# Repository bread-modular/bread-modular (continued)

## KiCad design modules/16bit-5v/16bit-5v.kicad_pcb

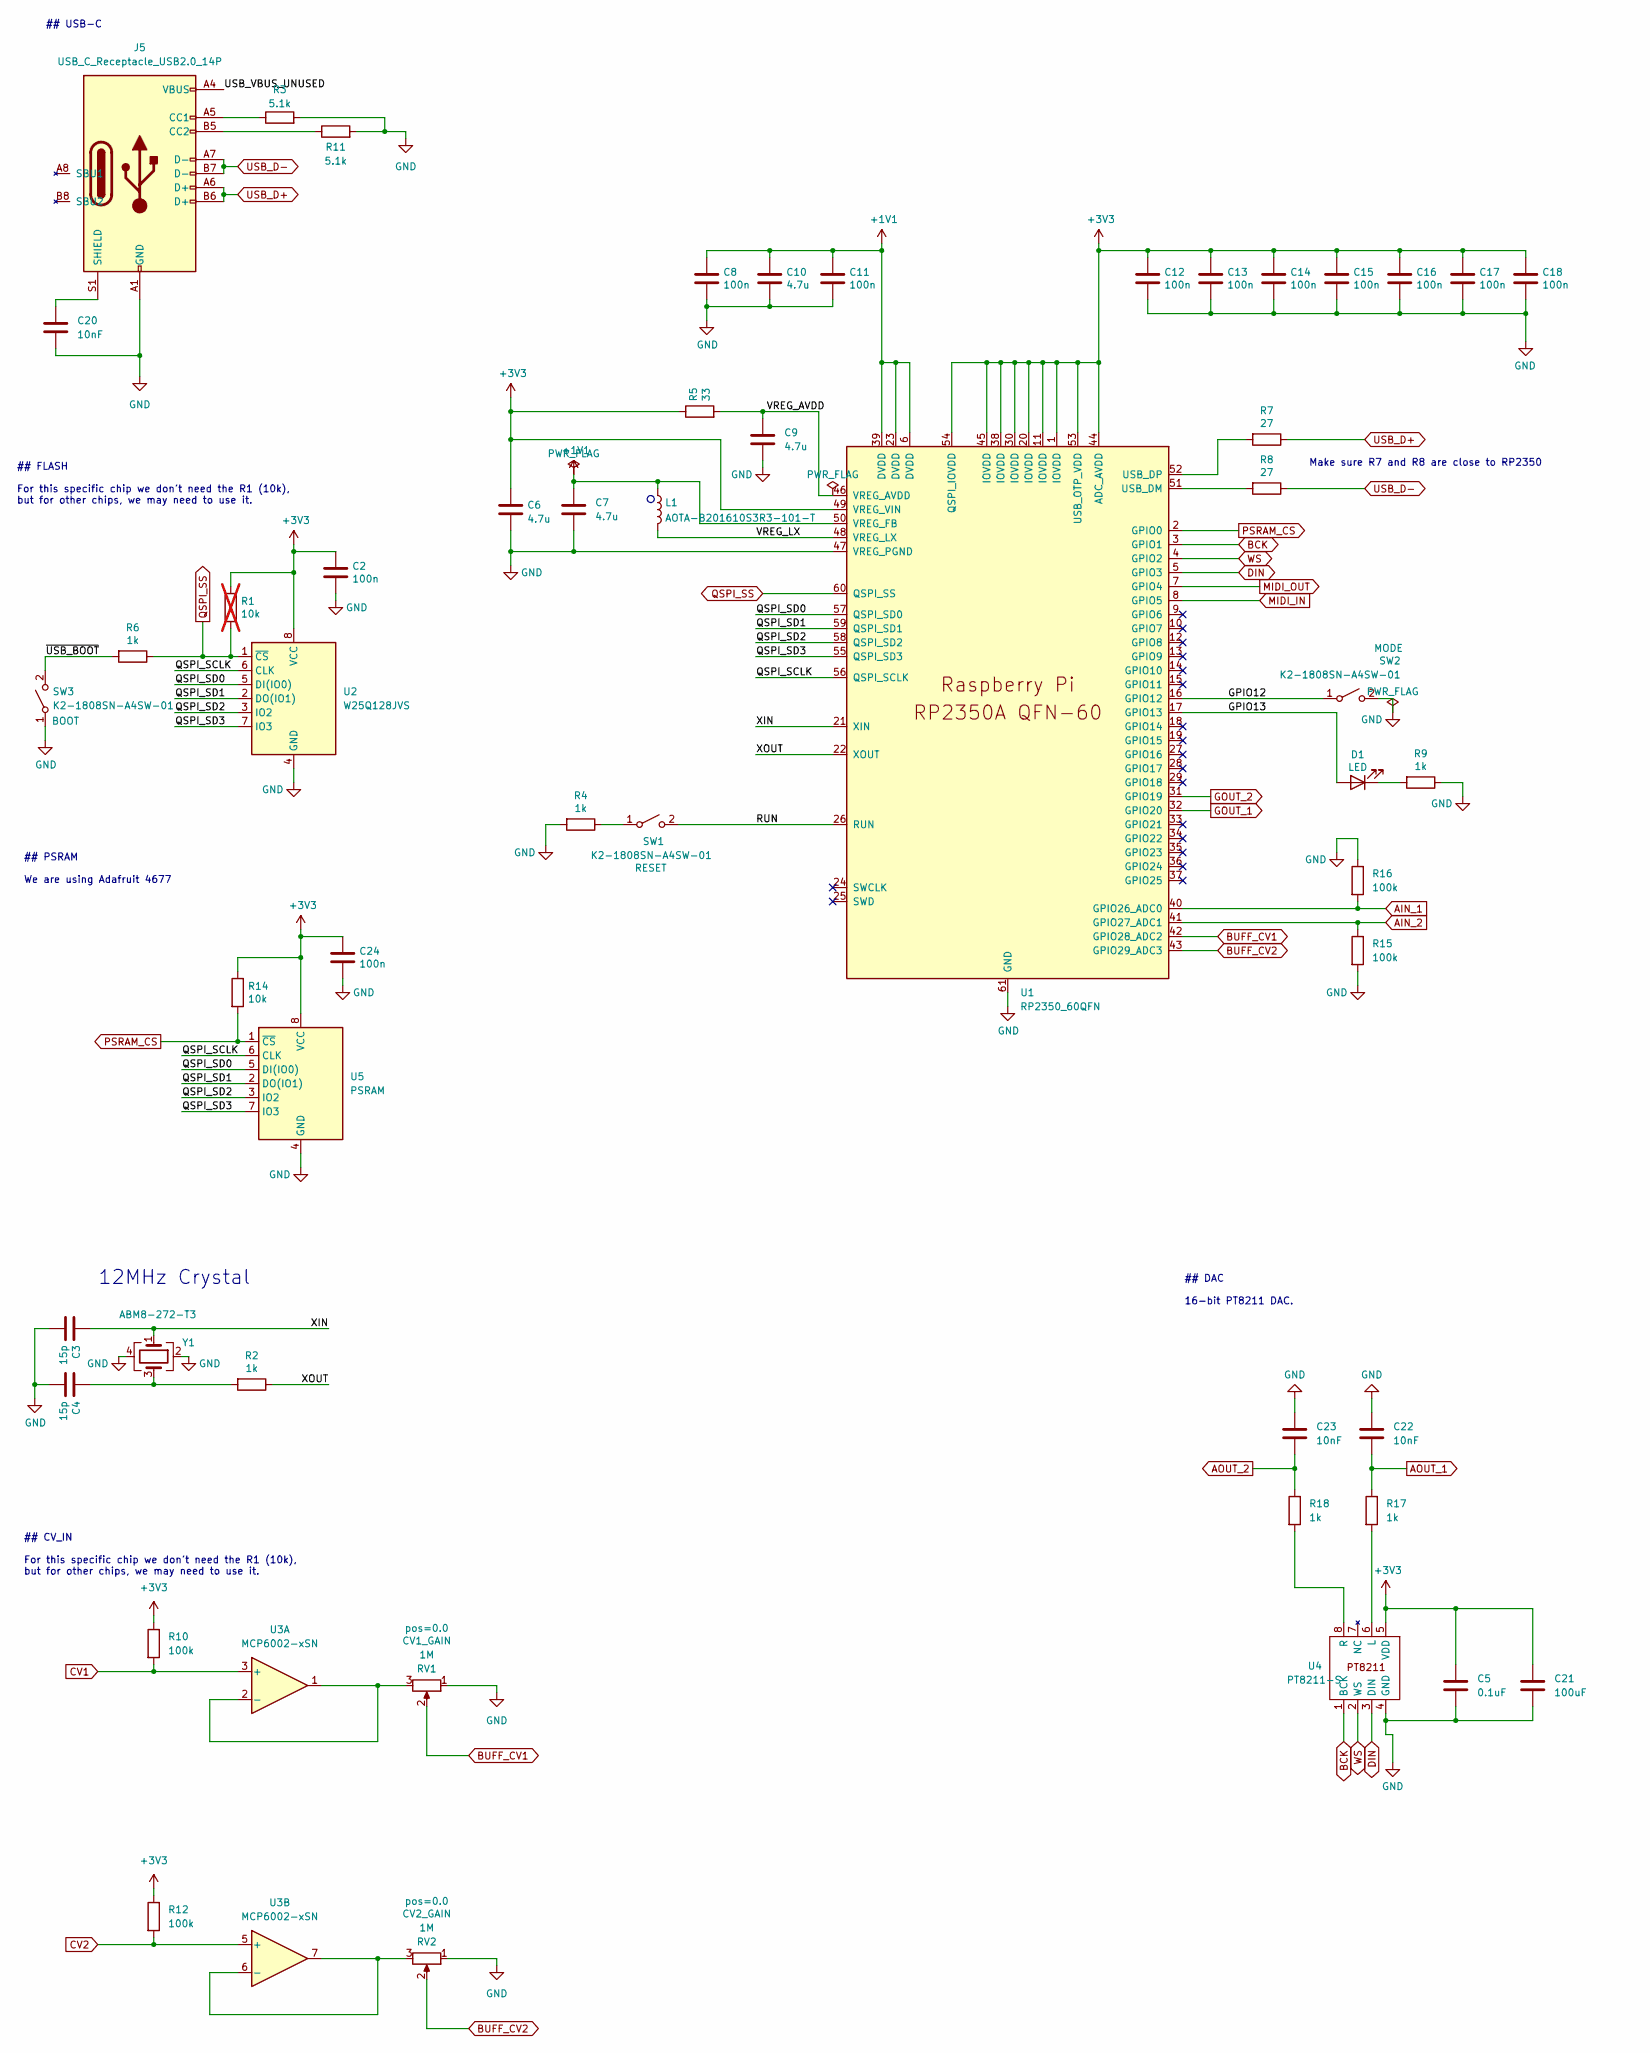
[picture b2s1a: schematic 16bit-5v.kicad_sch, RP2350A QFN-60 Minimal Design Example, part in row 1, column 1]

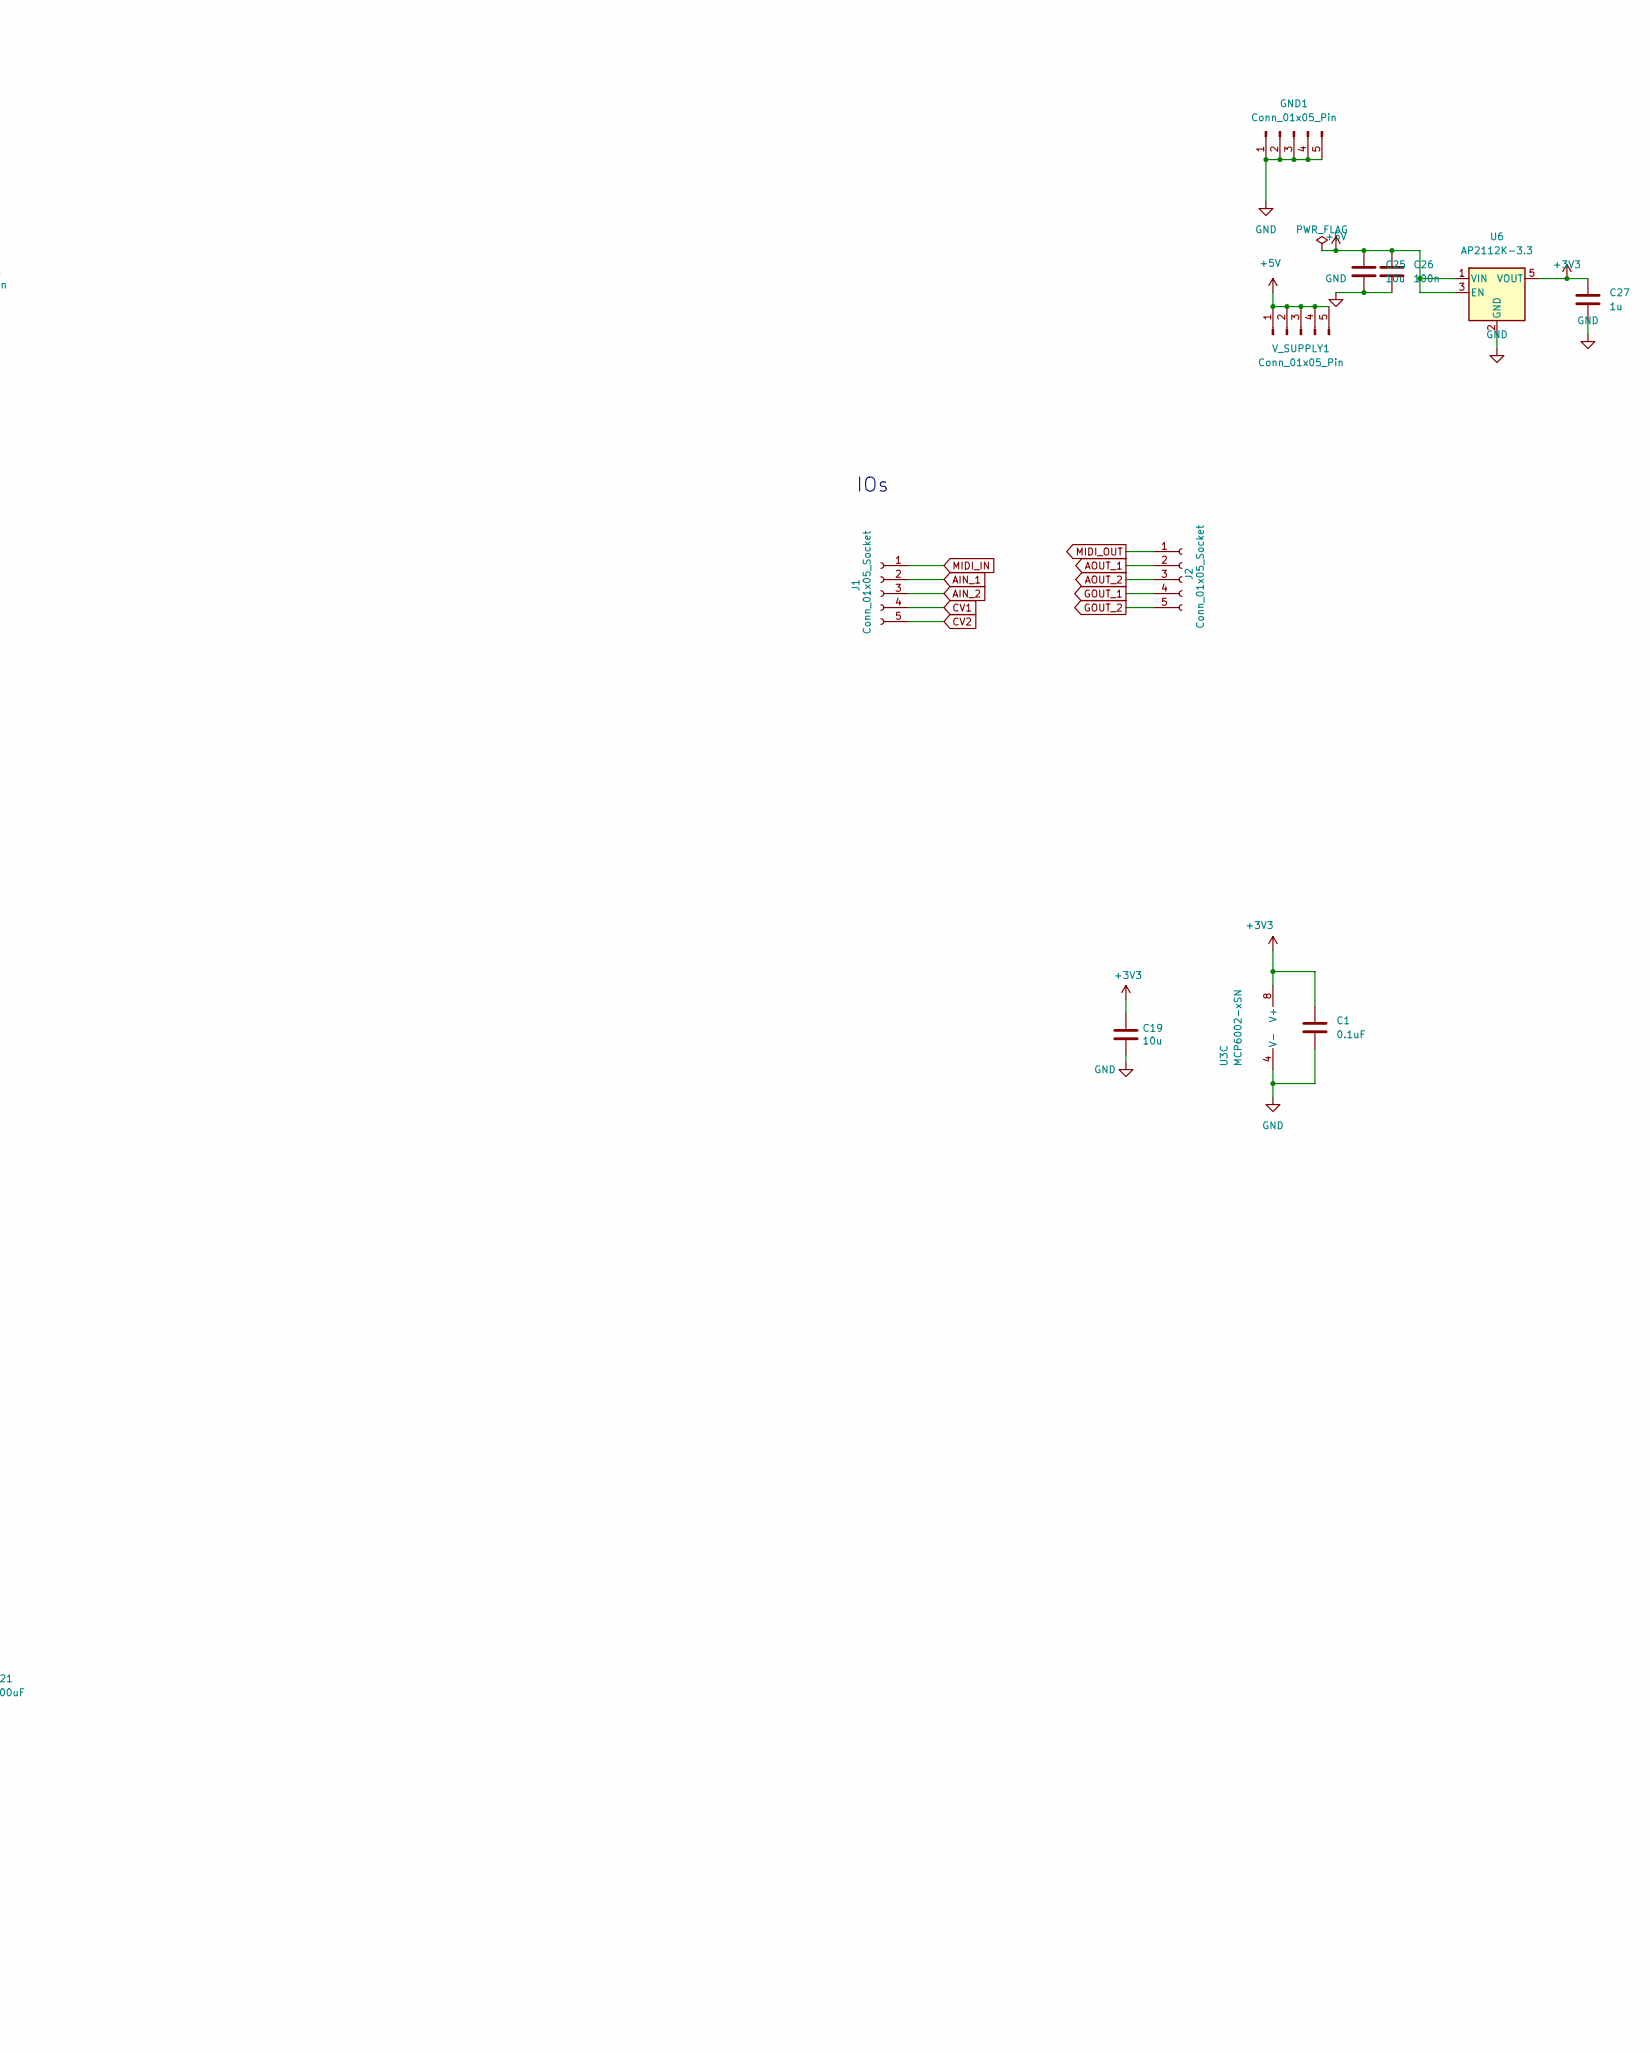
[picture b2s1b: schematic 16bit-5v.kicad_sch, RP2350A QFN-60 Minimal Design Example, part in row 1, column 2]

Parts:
C1, C5: 0.1uF; C_0402_1005Metric; Voltage Rating 16 V; Tolerance ±10%; MPN CL05B104KO5NNNC; LCSC C1525
C2, C8, C11, C12, C13, C14, C15, C16, C17, C18, C24, C26: 100n; C_0402_1005Metric; Voltage Rating 16 V; Tolerance ±10%; MPN CL05B104KO5NNNC; LCSC C1525
C3, C4: 15p; C_0402_1005Metric; Voltage Rating 50 V; Tolerance ±5%; MPN 0402CG150J500NT; LCSC C1548
C6, C7: 4.7u; C_0402_1005Metric_small_pads; Voltage Rating 10 V; Tolerance ±20%; MPN CL05A475MP5NRNC; LCSC C23733
C9, C10: 4.7u; C_0402_1005Metric; Voltage Rating 10 V; Tolerance ±20%; MPN CL05A475MP5NRNC; LCSC C23733
C19, C25: 10u; C_0805_2012Metric; Voltage Rating 25 V; Tolerance ±10%; MPN CL21A106KAYNNNE; LCSC C15850
C20: 10nF; C_0805_2012Metric; Voltage Rating 50 V; Tolerance ±10%; MPN CL21B103KBANNNC; LCSC C1710
C21: 100uF; C_1206_3216Metric; Voltage Rating 6.3 V; Tolerance ±20%; MPN CL31A107MQHNNNE; LCSC C15008
C22, C23: 10nF; C_0402_1005Metric; Voltage Rating 50 V; Tolerance ±10%; MPN CL05B103KB5NNNC; LCSC C15195
C27: 1u; C_0805_2012Metric; Voltage Rating 50 V; Tolerance ±10%; MPN CL21B105KBFNNNE; LCSC C28323
D1: LED; LED_0603_1608Metric
GND1: Conn_01x05_Pin; PinHeader_1x05_P2.54mm_Vertical
J1, J2: Conn_01x05_Socket; PinSocket_1x05_P2.54mm_Vertical
J5: USB_C_Receptacle_USB2.0_14P; HRO-TYPE-C-31-M-12; MPN TYPE-C-31-M-12; JLCPCB Position Offset X 0
L1: AOTA-B201610S3R3-101-T; L_pol_2016; MPN AOTA-B201610S3R3-101-T; LCSC C42411119
R1: 10k; R_0402_1005Metric; not fitted
R2, R4, R6, R9, R17, R18: 1k; R_0402_1005Metric; Voltage Rating 50 V; Tolerance ±1%; MPN 0402WGF1001TCE; LCSC C11702
R3, R11: 5.1k; R_0603_1608Metric; Voltage Rating 75 V; Tolerance ±1%; MPN 0603WAF5101T5E; LCSC C23186
R5: 33; R_0402_1005Metric; Voltage Rating 50 V; Tolerance ±1%; MPN 0402WGF330JTCE; LCSC C25105
R7, R8: 27; R_0402_1005Metric
R10, R12, R15, R16: 100k; R_0402_1005Metric; Voltage Rating 50 V; Tolerance ±1%; MPN 0402WGF1003TCE; LCSC C25741
R14: 10k; R_0402_1005Metric; Voltage Rating 50 V; Tolerance ±1%; MPN 0402WGF1002TCE; LCSC C25744
RV1, RV2: 1M; Potentiometer_RV09
SW1, SW2, SW3: K2-1808SN-A4SW-01; MPN K2-1808SN-A4SW-01; LCSC C92589
U1: RP2350_60QFN; RP2350-QFN-60-1EP_7x7_P0.4mm_EP3.4x3.4mm_ThermalVias; MPN RP2350A; LCSC C42411118
U2: W25Q128JVS; SOIC-8_5.23x5.23mm_P1.27mm; MPN W25Q128JVSIQ; LCSC C97521
U3: MCP6002-xSN; SOIC-8_3.9x4.9mm_P1.27mm; MPN MCP6002-I/SN; LCSC C116706
U4: PT8211-S; SOIC-8_3.9x4.9mm_P1.27mm; MPN PT8211-S; LCSC C92004
U5: PSRAM; SOIC-8 Generic
U6: AP2112K-3.3; SOT-23-5; MPN AP2112K-3.3TRG1; LCSC C51118
V_SUPPLY1: Conn_01x05_Pin; PinHeader_1x05_P2.54mm_Vertical
Y1: ABM8-272-T3; Crystal_SMD_3225-4Pin_3.2x2.5mm; MPN ABM8-272-T3; LCSC C20625731

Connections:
+1V1: C7.1, C8.1, C10.1, C11.1, L1.1, U1.6 (DVDD), U1.23 (DVDD), U1.39 (DVDD), U1.50 (VREG_FB)
+3V3: C1.1, C2.1, C5.1, C6.1, C12.1, C13.1, C14.1, C15.1, C16.1, C17.1, C18.1, C19.1, C21.1, C24.1, C27.1, R1.1, R5.1, R10.1, R12.1, R14.1, U1.1 (IOVDD), U1.11 (IOVDD), U1.20 (IOVDD), U1.30 (IOVDD), U1.38 (IOVDD), U1.44 (ADC_AVDD), U1.45 (IOVDD), U1.49 (VREG_VIN), U1.53 (USB_OTP_VDD), U1.54 (QSPI_IOVDD), U2.8 (VCC), U3.8 (V+), U4.5 (VDD), U5.8 (VCC), U6.5 (VOUT)
+5V: C25.1, C26.1, U6.1 (VIN), U6.3 (EN), V_SUPPLY1.1, V_SUPPLY1.2, V_SUPPLY1.3, V_SUPPLY1.4, V_SUPPLY1.5
/GPIO12: SW2.1 (A), U1.16 (GPIO12)
/GPIO13: D1.2 (A), U1.17 (GPIO13)
/QSPI_SCLK: U1.56 (QSPI_SCLK), U2.6 (CLK), U5.6 (CLK)
/QSPI_SD0: U1.57 (QSPI_SD0), U2.5 (DI(IO0)), U5.5 (DI(IO0))
/QSPI_SD1: U1.59 (QSPI_SD1), U2.2 (DO(IO1)), U5.2 (DO(IO1))
/QSPI_SD2: U1.58 (QSPI_SD2), U2.3 (IO2), U5.3 (IO2)
/QSPI_SD3: U1.55 (QSPI_SD3), U2.7 (IO3), U5.7 (IO3)
/RUN: SW1.2 (B), U1.26 (RUN)
/USB_VBUS_UNUSED: J5.A4 (VBUS), J5.A9 (VBUS)
/VREG_AVDD: C9.1, R5.2, U1.46 (VREG_AVDD)
/VREG_LX: L1.2, U1.48 (VREG_LX)
/XIN: C3.1, U1.21 (XIN), Y1.1
/XOUT: R2.1, U1.22 (XOUT)
/~USB_BOOT: R6.2, SW3.2 (B)
AIN_1: J1.2, R16.2, U1.40 (GPIO26_ADC0)
AIN_2: J1.3, R15.1, U1.41 (GPIO27_ADC1)
AOUT_1: C22.2, J2.2, R17.1
AOUT_2: C23.2, J2.3, R18.1
BCK: U1.3 (GPIO1), U4.1 (BCK)
BUFF_CV1: RV1.2, U1.42 (GPIO28_ADC2)
BUFF_CV2: RV2.2, U1.43 (GPIO29_ADC3)
CV1: J1.4, R10.2, U3.3 (+)
CV2: J1.5, R12.2, U3.5 (+)
DIN: U1.5 (GPIO3), U4.3 (DIN)
GND: C1.2, C2.2, C3.2, C4.2, C5.2, C6.2, C7.2, C8.2, C9.2, C10.2, C11.2, C12.2, C13.2, C14.2, C15.2, C16.2, C17.2, C18.2, C19.2, C20.2, C21.2, C22.1, C23.1, C24.2, C25.2, C26.2, C27.2, GND1.1, GND1.2, GND1.3, GND1.4, GND1.5, J5.A1 (GND), J5.A12 (GND), R3.2, R4.2, R9.1, R11.2, R15.2, R16.1, RV1.1, RV2.1, SW2.2 (B), SW3.1 (A), U1.47 (VREG_PGND), U1.61 (GND), U2.4 (GND), U3.4 (V-), U4.4 (GND), U5.4 (GND), U6.2 (GND), Y1.2, Y1.4
GOUT_1: J2.4, U1.32 (GPIO20)
GOUT_2: J2.5, U1.31 (GPIO19)
MIDI_IN: J1.1, U1.8 (GPIO5)
MIDI_OUT: J2.1, U1.7 (GPIO4)
unnamed: C4.1, R2.2, Y1.3
unnamed: D1.1 (K), R9.2
unnamed: J5.A5 (CC1), R3.1
unnamed: J5.B5 (CC2), R11.1
unnamed: C20.1, J5.S1 (SHIELD)
unnamed: R4.1, SW1.1 (A)
unnamed: R8.2, U1.51 (USB_DM)
unnamed: R7.2, U1.52 (USB_DP)
unnamed: RV1.3, U3.1, U3.2 (-)
unnamed: RV2.3, U3.6 (-), U3.7
unnamed: R17.2, U4.6 (L)
unnamed: R18.2, U4.8 (R)
PSRAM_CS: R14.2, U1.2 (GPIO0), U5.1 (~CS)
QSPI_SS: R1.2, R6.1, U1.60 (QSPI_SS), U2.1 (~CS)
USB_D+: J5.A6 (D+), J5.B6 (D+), R7.1
USB_D-: J5.A7 (D-), J5.B7 (D-), R8.1
WS: U1.4 (GPIO2), U4.2 (WS)

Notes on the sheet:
IOs
## FLASH For this specific chip we don't need the R1 (10k), but for other chips, we may need to use it.
## PSRAM We are using Adafruit 4677
## DAC 16-bit PT8211 DAC.
## USB-C
Make sure R7 and R8 are close to RP2350
12MHz Crystal
## CV_IN For this specific chip we don't need the R1 (10k), but for other chips, we may need to use it.

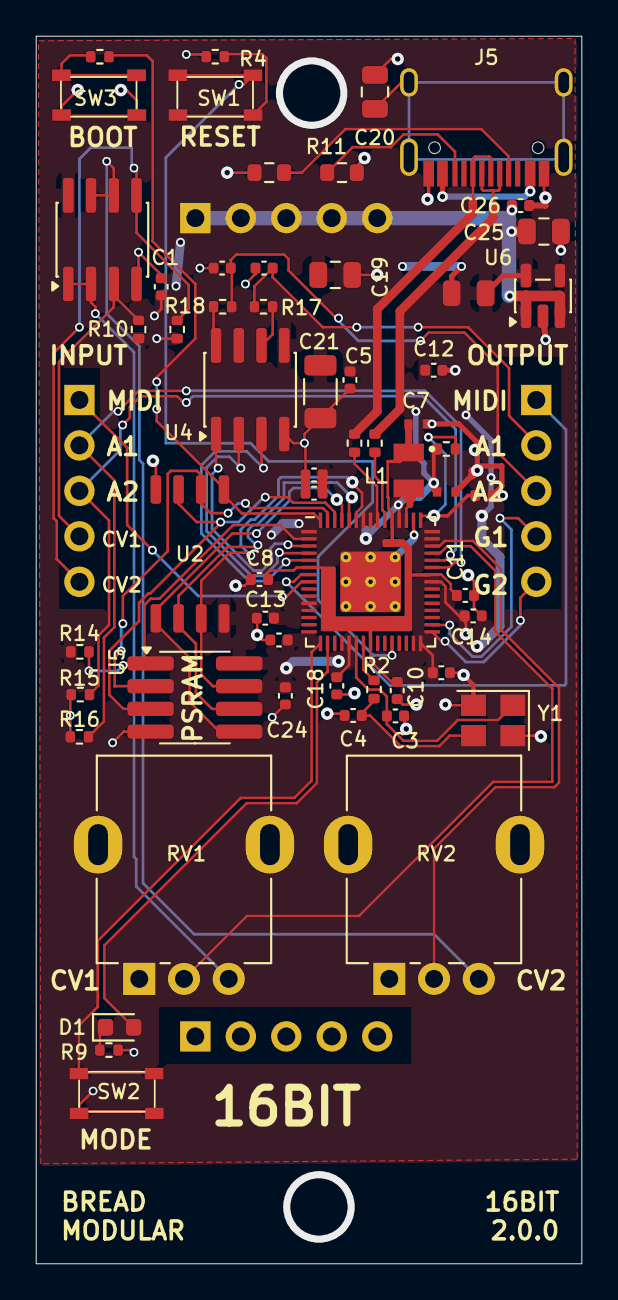
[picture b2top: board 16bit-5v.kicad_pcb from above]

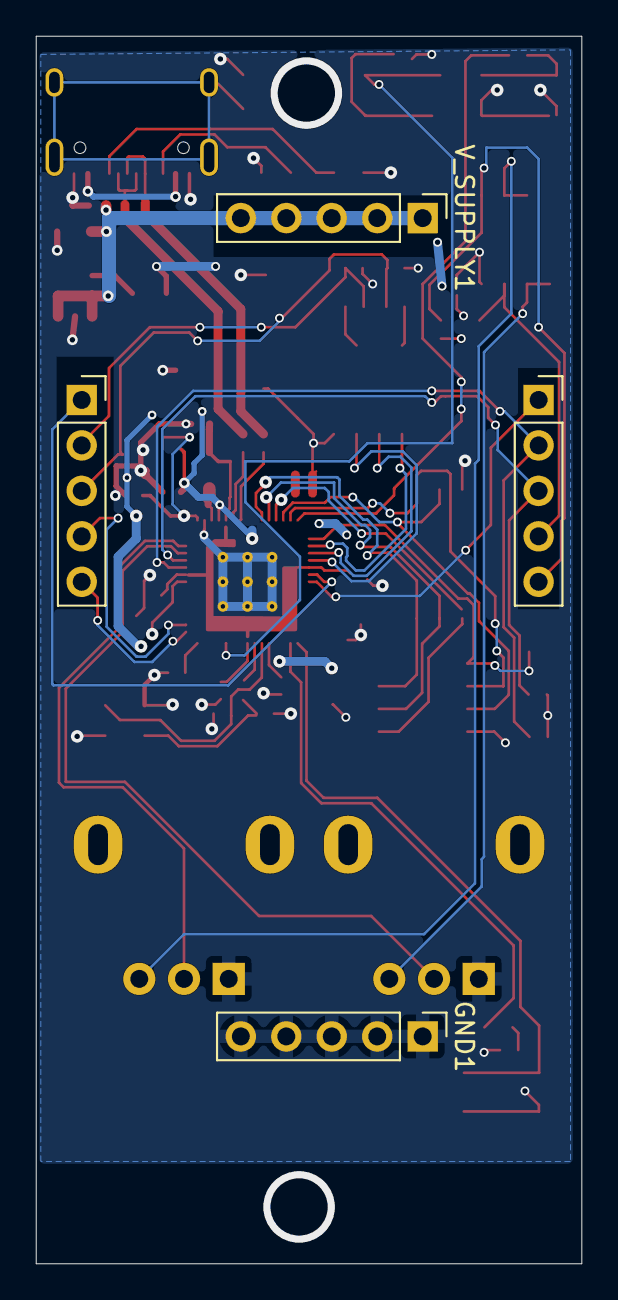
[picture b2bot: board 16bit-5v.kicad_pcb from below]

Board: 2 copper layers, 30.5 x 68.6 mm, 62 parts (4 on the bottom side), 49 nets.

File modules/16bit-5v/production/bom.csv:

Comment,Designator,Footprint,LCSC Part #,Quantity,Manufacturer,MPN
0.1uF,"C1, C5",C_0402_1005Metric,C1525,2,Samsung Electro-Mechanics,CL05B104KO5NNNC
100n,"C2, C8, C11, C12, C13, C14, C15, C16, C17, C18, C24, C26",C_0402_1005Metric,C1525,12,Samsung Electro-Mechanics,CL05B104KO5NNNC
15p,"C3, C4",C_0402_1005Metric,C1548,2,FH (Guangdong Fenghua Advanced Tech),0402CG150J500NT
4.7u,"C6, C7",C_0402_1005Metric_small_pads,C23733,2,Samsung Electro-Mechanics,CL05A475MP5NRNC
4.7u,"C9, C10",C_0402_1005Metric,C23733,2,Samsung Electro-Mechanics,CL05A475MP5NRNC
10u,"C19, C25",C_0805_2012Metric,C15850,2,Samsung Electro-Mechanics,CL21A106KAYNNNE
10nF,C20,C_0805_2012Metric,C1710,1,Samsung Electro-Mechanics,CL21B103KBANNNC
100uF,C21,C_1206_3216Metric,C15008,1,Samsung Electro-Mechanics,CL31A107MQHNNNE
10nF,"C22, C23",C_0402_1005Metric,C15195,2,Samsung Electro-Mechanics,CL05B103KB5NNNC
1u,C27,C_0805_2012Metric,C28323,1,Samsung Electro-Mechanics,CL21B105KBFNNNE
LED,D1,LED_0603_1608Metric,,1,,
Conn_01x05_Pin,"GND1, V_SUPPLY1",PinHeader_1x05_P2.54mm_Vertical,,2,,
Conn_01x05_Socket,"J1, J2",PinSocket_1x05_P2.54mm_Vertical,,2,,
USB_C_Receptacle_USB2.0_14P,J5,HRO-TYPE-C-31-M-12,C165948,1,Korean Hroparts Elec,TYPE-C-31-M-12
AOTA-B201610S3R3-101-T,L1,L_pol_2016,C42411119,1,Abracon LLC,AOTA-B201610S3R3-101-T
1k,"R2, R4, R6, R9, R17, R18",R_0402_1005Metric,C11702,6,UNI-ROYAL(Uniroyal Elec),0402WGF1001TCE
5.1k,"R3, R11",R_0603_1608Metric,C23186,2,UNI-ROYAL(Uniroyal Elec),0603WAF5101T5E
33,R5,R_0402_1005Metric,C25105,1,UNI-ROYAL(Uniroyal Elec),0402WGF330JTCE
27,"R7, R8",R_0402_1005Metric,,2,,
100k,"R10, R12, R15, R16",R_0402_1005Metric,C25741,4,UNI-ROYAL(Uniroyal Elec),0402WGF1003TCE
10k,R14,R_0402_1005Metric,C25744,1,UNI-ROYAL(Uniroyal Elec),0402WGF1002TCE
1M,"RV1, RV2",Potentiometer_RV09,,2,,
K2-1808SN-A4SW-01,"SW1, SW2, SW3",K2-1808SN-A4SW-01,C92589,3,Korean Hroparts Elec,K2-1808SN-A4SW-01
RP2350_60QFN,U1,RP2350-QFN-60-1EP_7x7_P0.4mm_EP3.4x3.4mm_ThermalVias,C42411118,1,Raspberry Pi,RP2350A
W25Q128JVS,U2,SOIC-8_5.23x5.23mm_P1.27mm,C97521,1,Winbond Elec,W25Q128JVSIQ
MCP6002-xSN,U3,SOIC-8_3.9x4.9mm_P1.27mm,C116706,1,Microchip Tech,MCP6002-I/SN
PT8211-S,U4,SOIC-8_3.9x4.9mm_P1.27mm,C92004,1,PTC(Princeton Tech),PT8211-S
PSRAM,U5,SOIC-8 Generic,,1,,
AP2112K-3.3,U6,SOT-23-5,C51118,1,Diodes Incorporated,AP2112K-3.3TRG1
ABM8-272-T3,Y1,Crystal_SMD_3225-4Pin_3.2x2.5mm,C20625731,1,Abracon LLC,ABM8-272-T3

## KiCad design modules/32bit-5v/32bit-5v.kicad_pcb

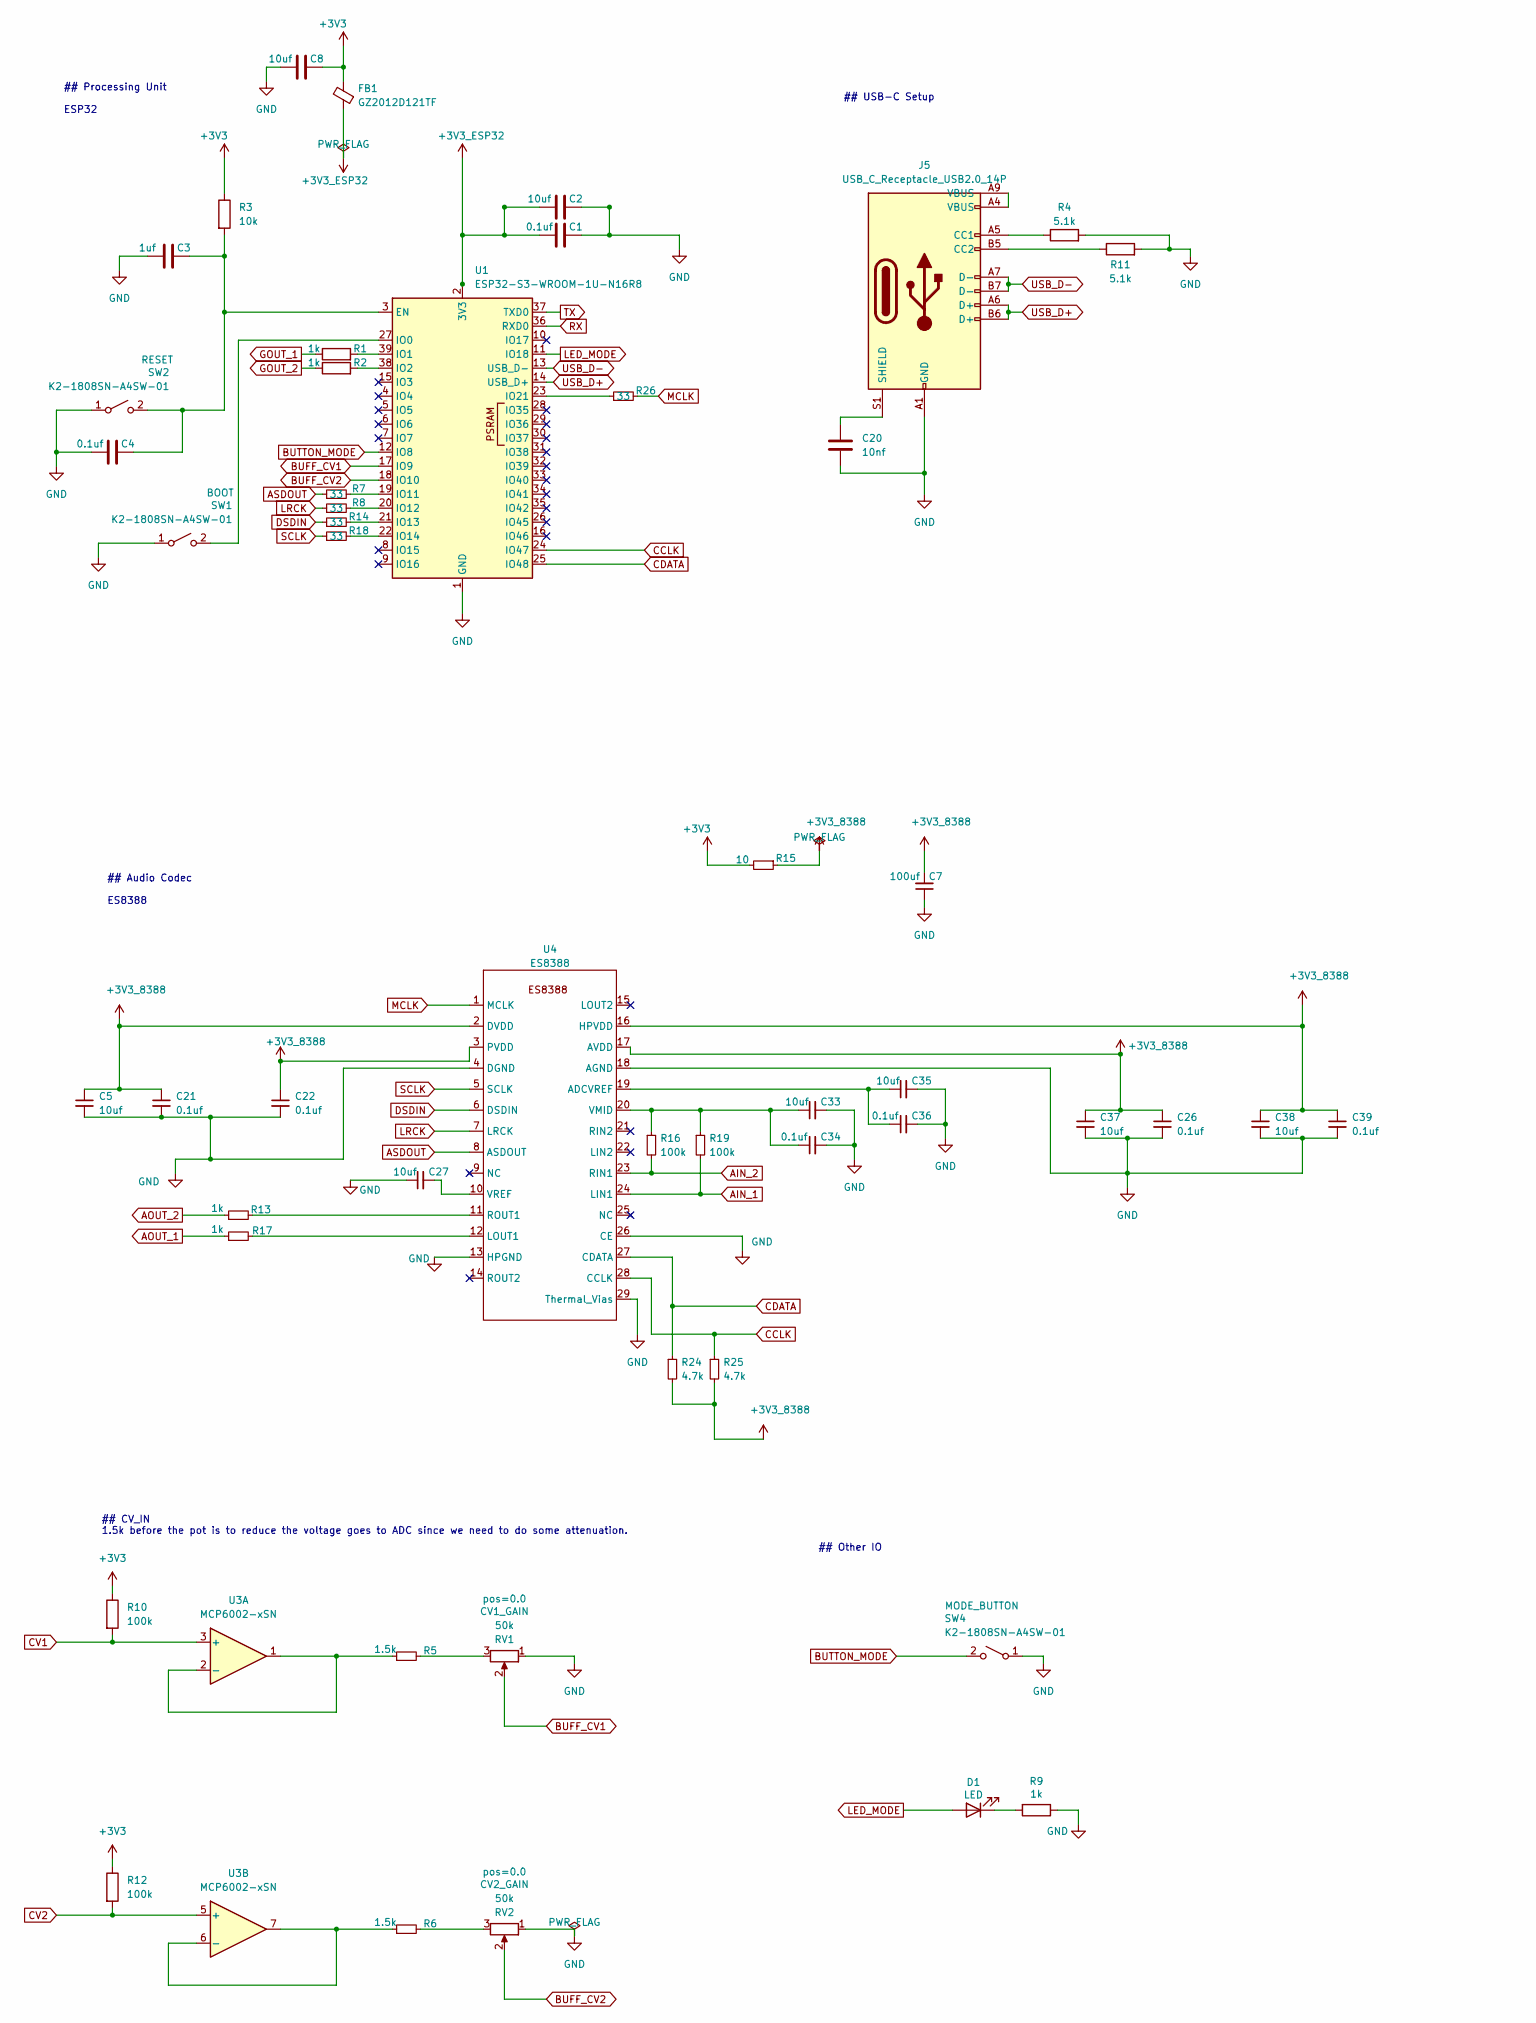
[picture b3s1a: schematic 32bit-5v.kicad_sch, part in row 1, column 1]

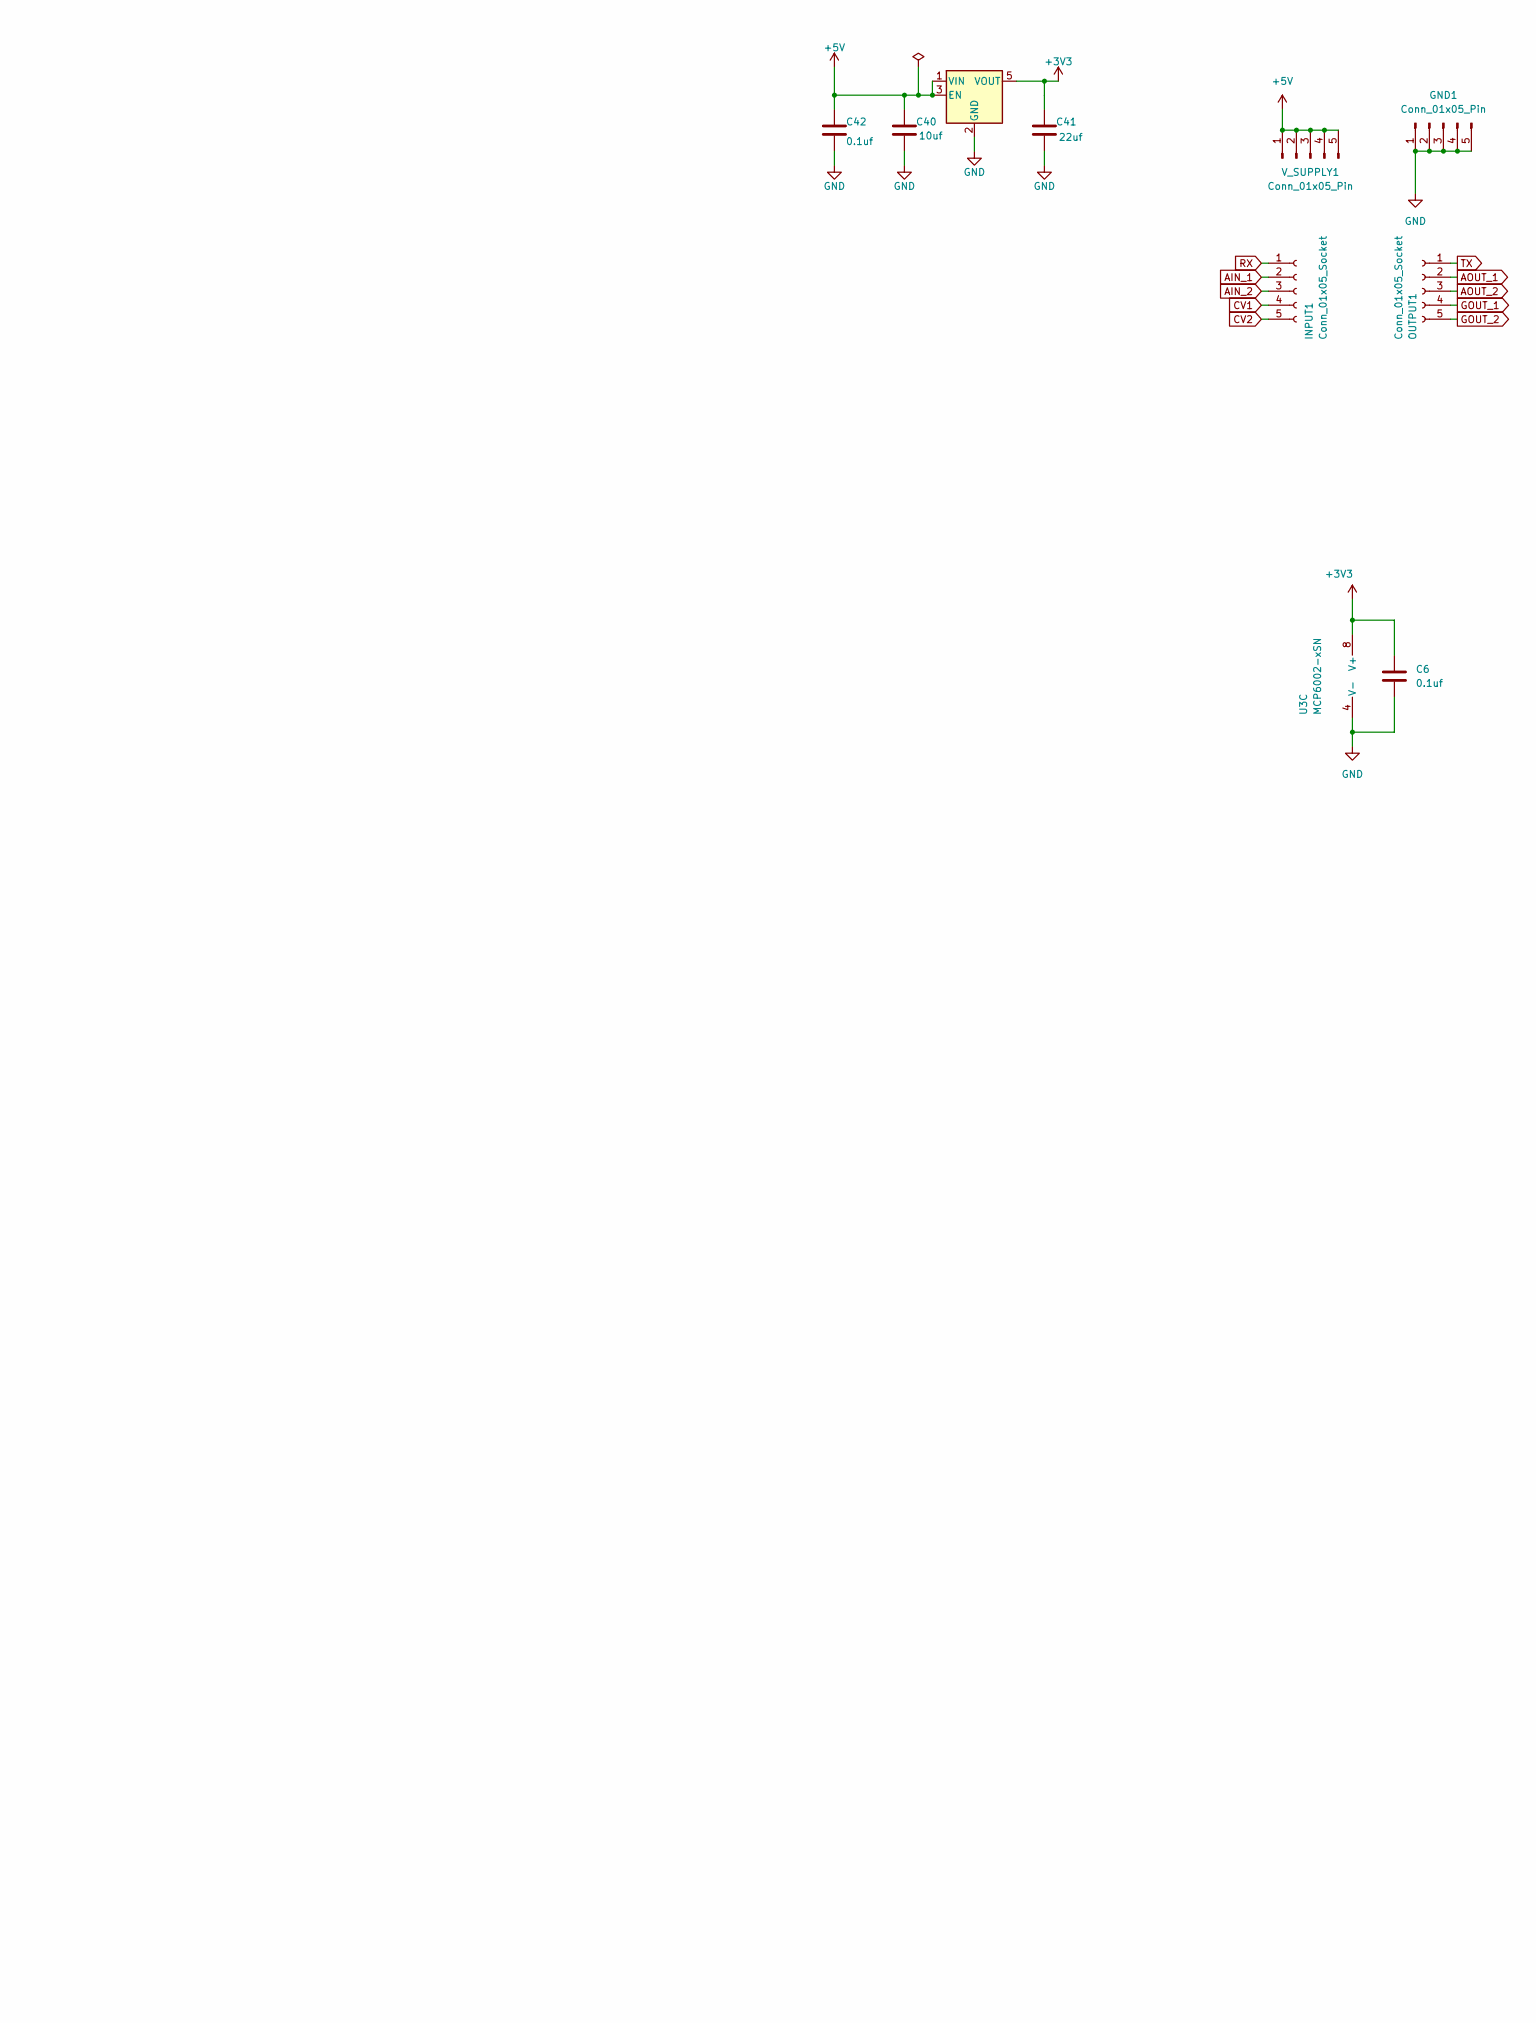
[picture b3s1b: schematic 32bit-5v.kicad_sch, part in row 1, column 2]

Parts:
C1, C4, C6, C21, C22, C26, C34, C36, C39, C42: 0.1uf; C_0402_1005Metric; Tolerance ±10%; Voltage Rating 16V; MPN CL05B104KO5NNNC; LCSC C1525
C2, C8: 10uf; C_0603_1608Metric; Tolerance ±10%; Voltage Rating 10V; MPN CL10A106KP8NNNC; LCSC C19702
C3: 1uf; C_0402_1005Metric; Tolerance ±10%; Voltage Rating 25V; MPN CL05A105KA5NQNC; LCSC C52923
C5, C27, C33, C35, C37, C38: 10uf; C_0402_1005Metric; Tolerance ±20%; Voltage Rating 6.3V; MPN CL05A106MQ5NUNC; LCSC C15525
C7: 100uf; C_1206_3216Metric; Tolerance ±20%; Voltage Rating 6.3V; MPN CL31A107MQHNNNE; LCSC C15008
C20: 10nf; C_0805_2012Metric; Tolerance ±10%; Voltage Rating 50V; MPN CL21B103KBANNNC; LCSC C1710
C40: 10uf; C_0805_2012Metric; Tolerance ±10%; Voltage Rating 25V; MPN CL21A106KAYNNNE; LCSC C15850
C41: 22uf; C_0805_2012Metric; Tolerance ±20%; Voltage Rating 25V; MPN CL21A226MAQNNNE; LCSC C45783
D1: LED; LED_0603_1608Metric
FB1: GZ2012D121TF; C_0805_2012Metric; MPN GZ2012D121TF; LCSC C5671
GND1: Conn_01x05_Pin; Power_Connector
INPUT1: Conn_01x05_Socket; PinSocket_1x05_P2.54mm_Vertical
J5: USB_C_Receptacle_USB2.0_14P; HRO-TYPE-C-31-M-12; MPN TYPE-C-31-M-12; LCSC C165948
OUTPUT1: Conn_01x05_Socket; PinSocket_1x05_P2.54mm_Vertical
R1, R2, R9, R13, R17: 1k; R_0402_1005Metric; Tolerance ±1%; Voltage Rating 50V; MPN 0402WGF1001TCE; LCSC C11702
R3: 10k; R_0402_1005Metric; Tolerance ±1%; Voltage Rating 50V; MPN 0402WGF1002TCE; LCSC C25744
R4, R11: 5.1k; R_0603_1608Metric; Tolerance ±1%; Voltage Rating 75V; MPN 0603WAF5101T5E; LCSC C23186
R5, R6: 1.5k; R_0402_1005Metric; Tolerance ±1%; Voltage Rating 50V; MPN 0402WGF1501TCE; LCSC C25867
R7, R8, R14, R18, R26: 33; R_0402_1005Metric; Tolerance ±1%; Voltage Rating 50V; MPN 0402WGF330JTCE; LCSC C25105
R10, R12, R16, R19: 100k; R_0402_1005Metric; Tolerance ±1%; Voltage Rating 50V; MPN 0402WGF1003TCE; LCSC C25741
R15: 10; R_0603_1608Metric; Tolerance ±1%; Voltage Rating 75V; MPN 0603WAF100JT5E; LCSC C22859
R24, R25: 4.7k; R_0402_1005Metric; Tolerance ±1%; Voltage Rating 50V; MPN 0402WGF4701TCE; LCSC C25900
RV1, RV2: 50k; Potentiometer_RV09
SW1, SW2, SW4: K2-1808SN-A4SW-01; MPN K2-1808SN-A4SW-01; LCSC C92589
U1: ESP32-S3-WROOM-1U-N16R8; ESP32-S3-WROOM-1U; MPN ESP32-S3-WROOM-1U-N16R8; LCSC C3013946
U3: MCP6002-xSN; SOIC-8_3.9x4.9mm_P1.27mm; MPN MCP6002-I/SN; LCSC C116706
U4: ES8388; ES8388_QFN28_4x4_P0.45_EP2.6_ThermalVias; MPN ES8388; LCSC C365736
U5: AP2112K-3.3; SOT-23-5; MPN AP2112K-3.3TRG1; LCSC C51118
V_SUPPLY1: Conn_01x05_Pin; Power_Connector

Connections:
+3V3: C6.1, C8.2, C41.1, FB1.2, R3.1, R10.1, R12.1, R15.2, U3.8 (V+), U5.5 (VOUT)
+3V3_8388: C5.1, C7.2, C21.1, C22.1, C26.1, C37.1, C38.1, C39.1, R15.1, R24.2, R25.2, U4.2 (DVDD), U4.3 (PVDD), U4.16 (HPVDD), U4.17 (AVDD)
+3V3_ESP32: C1.1, C2.1, FB1.1, U1.2 (3V3)
+5V: C40.1, C42.1, U5.1 (VIN), U5.3 (EN), V_SUPPLY1.1, V_SUPPLY1.2, V_SUPPLY1.3, V_SUPPLY1.4, V_SUPPLY1.5
AIN_1: INPUT1.2, R19.2, U4.24 (LIN1)
AIN_2: INPUT1.3, R16.2, U4.23 (RIN1)
AOUT_1: OUTPUT1.2, R17.1
AOUT_2: OUTPUT1.3, R13.1
ASDOUT: R7.1, U4.8 (ASDOUT)
BUFF_CV1: RV1.2, U1.17 (IO9)
BUFF_CV2: RV2.2, U1.18 (IO10)
BUTTON_MODE: SW4.2 (B), U1.12 (IO8)
CCLK: R25.1, U1.24 (IO47), U4.28 (CCLK)
CDATA: R24.1, U1.25 (IO48), U4.27 (CDATA)
CV1: INPUT1.4, R10.2, U3.3 (+)
CV2: INPUT1.5, R12.2, U3.5 (+)
DSDIN: R14.1, U4.6 (DSDIN)
GND: C1.2, C2.2, C3.1, C4.1, C5.2, C6.2, C7.1, C8.1, C20.2, C21.2, C22.2, C26.2, C27.1, C33.2, C34.2, C35.2, C36.2, C37.2, C38.2, C39.2, C40.2, C41.2, C42.2, GND1.1, GND1.2, GND1.3, GND1.4, GND1.5, J5.A1 (GND), J5.A12 (GND), R4.2, R9.1, R11.2, RV1.1, RV2.1, SW1.1 (A), SW2.1 (A), SW4.1 (A), U1.1 (GND), U1.40 (GND), U1.41 (GND), U3.4 (V-), U4.4 (DGND), U4.13 (HPGND), U4.18 (AGND), U4.26 (CE), U4.29 (Thermal_Vias), U5.2 (GND)
GOUT_1: OUTPUT1.4, R1.1
GOUT_2: OUTPUT1.5, R2.1
LED_MODE: D1.2 (A), U1.11 (IO18)
LRCK: R8.1, U4.7 (LRCK)
MCLK: R26.2, U4.1 (MCLK)
unnamed: D1.1 (K), R9.2
unnamed: J5.A5 (CC1), R4.1
unnamed: J5.B5 (CC2), R11.1
unnamed: C20.1, J5.S1 (SHIELD)
unnamed: J5.A4 (VBUS), J5.A9 (VBUS)
unnamed: R5.2, RV1.3
unnamed: R6.2, RV2.3
unnamed: SW1.2 (B), U1.27 (IO0)
unnamed: C3.2, C4.2, R3.2, SW2.2 (B), U1.3 (EN)
unnamed: R1.2, U1.39 (IO1)
unnamed: R2.2, U1.38 (IO2)
unnamed: R7.2, U1.19 (IO11)
unnamed: R8.2, U1.20 (IO12)
unnamed: R14.2, U1.21 (IO13)
unnamed: R18.2, U1.22 (IO14)
unnamed: R26.1, U1.23 (IO21)
unnamed: R5.1, U3.1, U3.2 (-)
unnamed: R6.1, U3.6 (-), U3.7
unnamed: C35.1, C36.1, U4.19 (ADCVREF)
unnamed: R17.2, U4.12 (LOUT1)
unnamed: R13.2, U4.11 (ROUT1)
unnamed: C33.1, C34.1, R16.1, R19.1, U4.20 (VMID)
unnamed: C27.2, U4.10 (VREF)
RX: INPUT1.1, U1.36 (RXD0)
SCLK: R18.1, U4.5 (SCLK)
TX: OUTPUT1.1, U1.37 (TXD0)
USB_D+: J5.A6 (D+), J5.B6 (D+), U1.14 (USB_D+)
USB_D-: J5.A7 (D-), J5.B7 (D-), U1.13 (USB_D-)

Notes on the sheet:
## Audio Codec ES8388
## CV_IN 1.5k before the pot is to reduce the voltage goes to ADC since we need to do some attenuation.
## Other IO
## USB-C Setup
## Processing Unit ESP32
